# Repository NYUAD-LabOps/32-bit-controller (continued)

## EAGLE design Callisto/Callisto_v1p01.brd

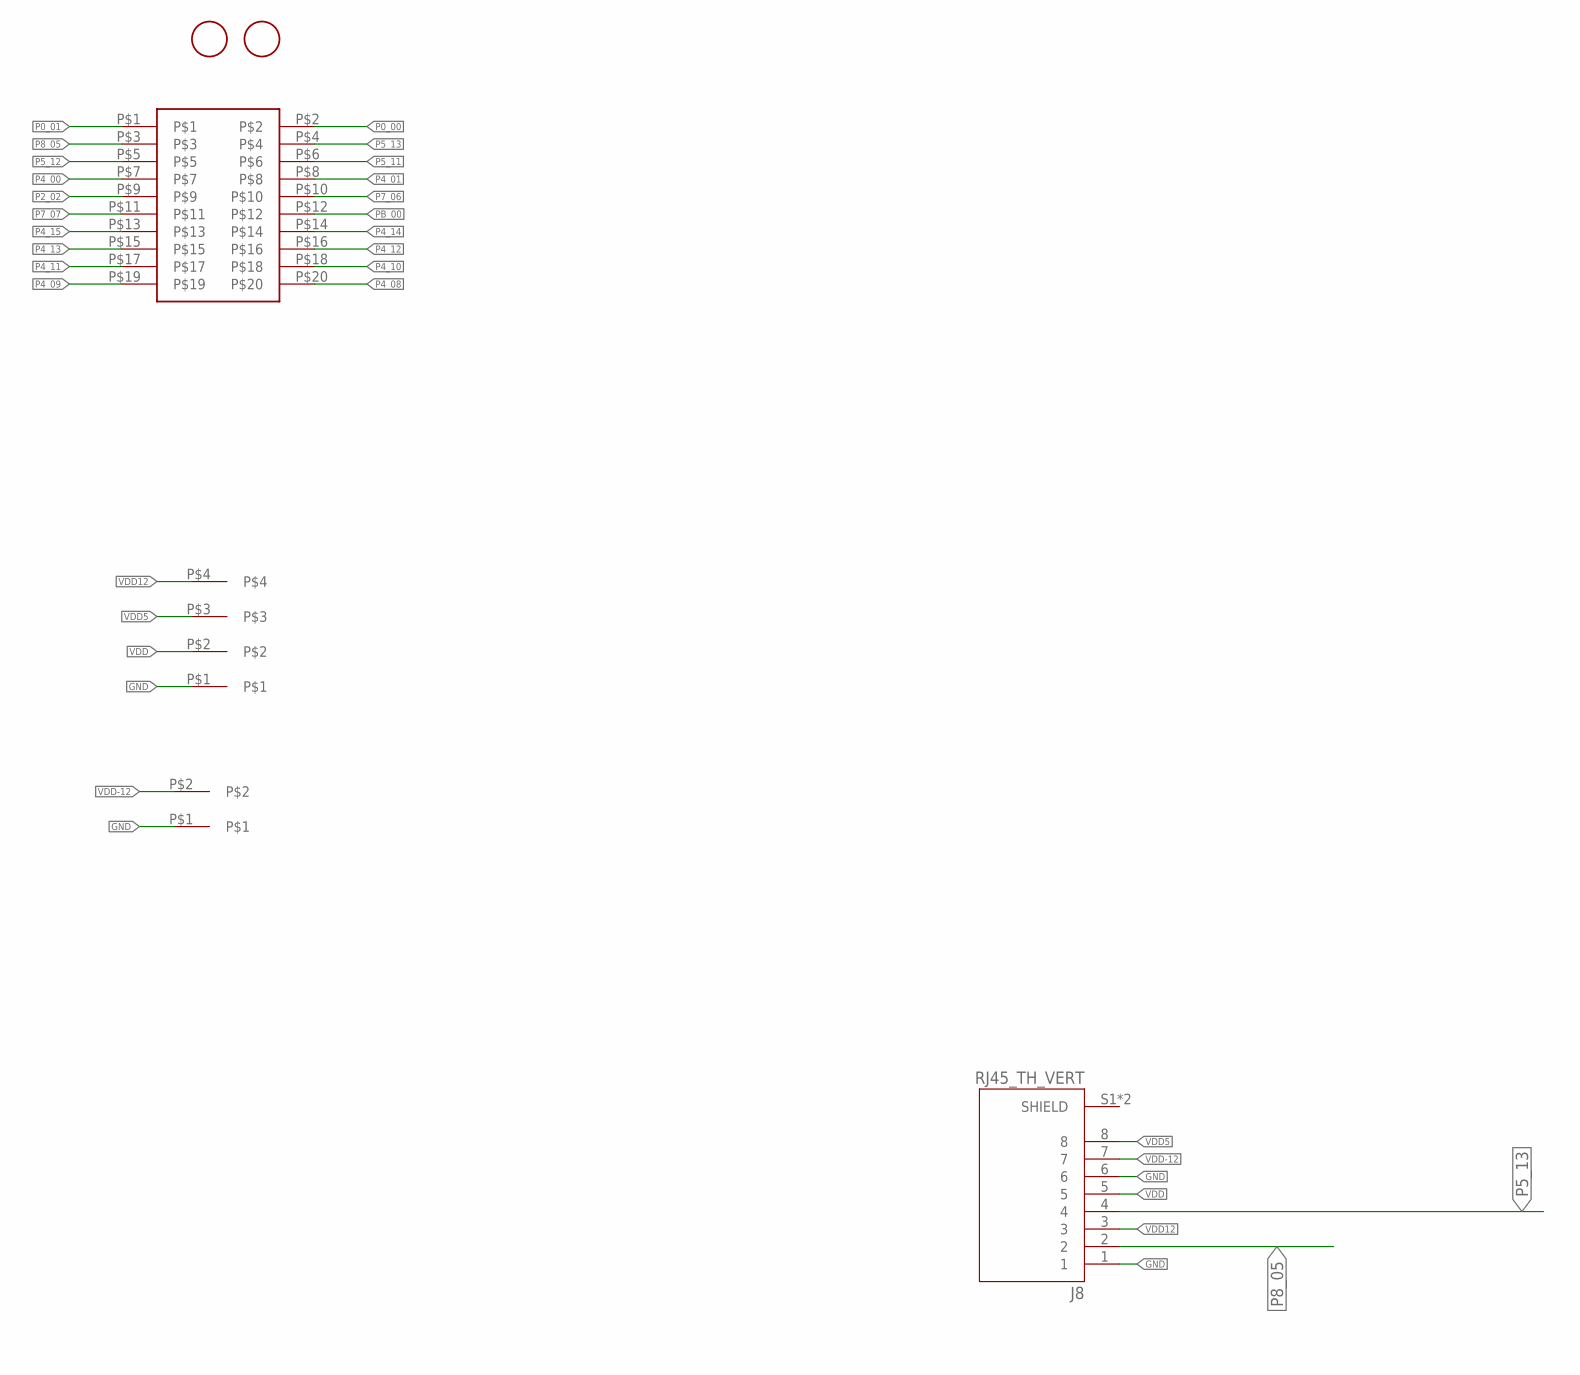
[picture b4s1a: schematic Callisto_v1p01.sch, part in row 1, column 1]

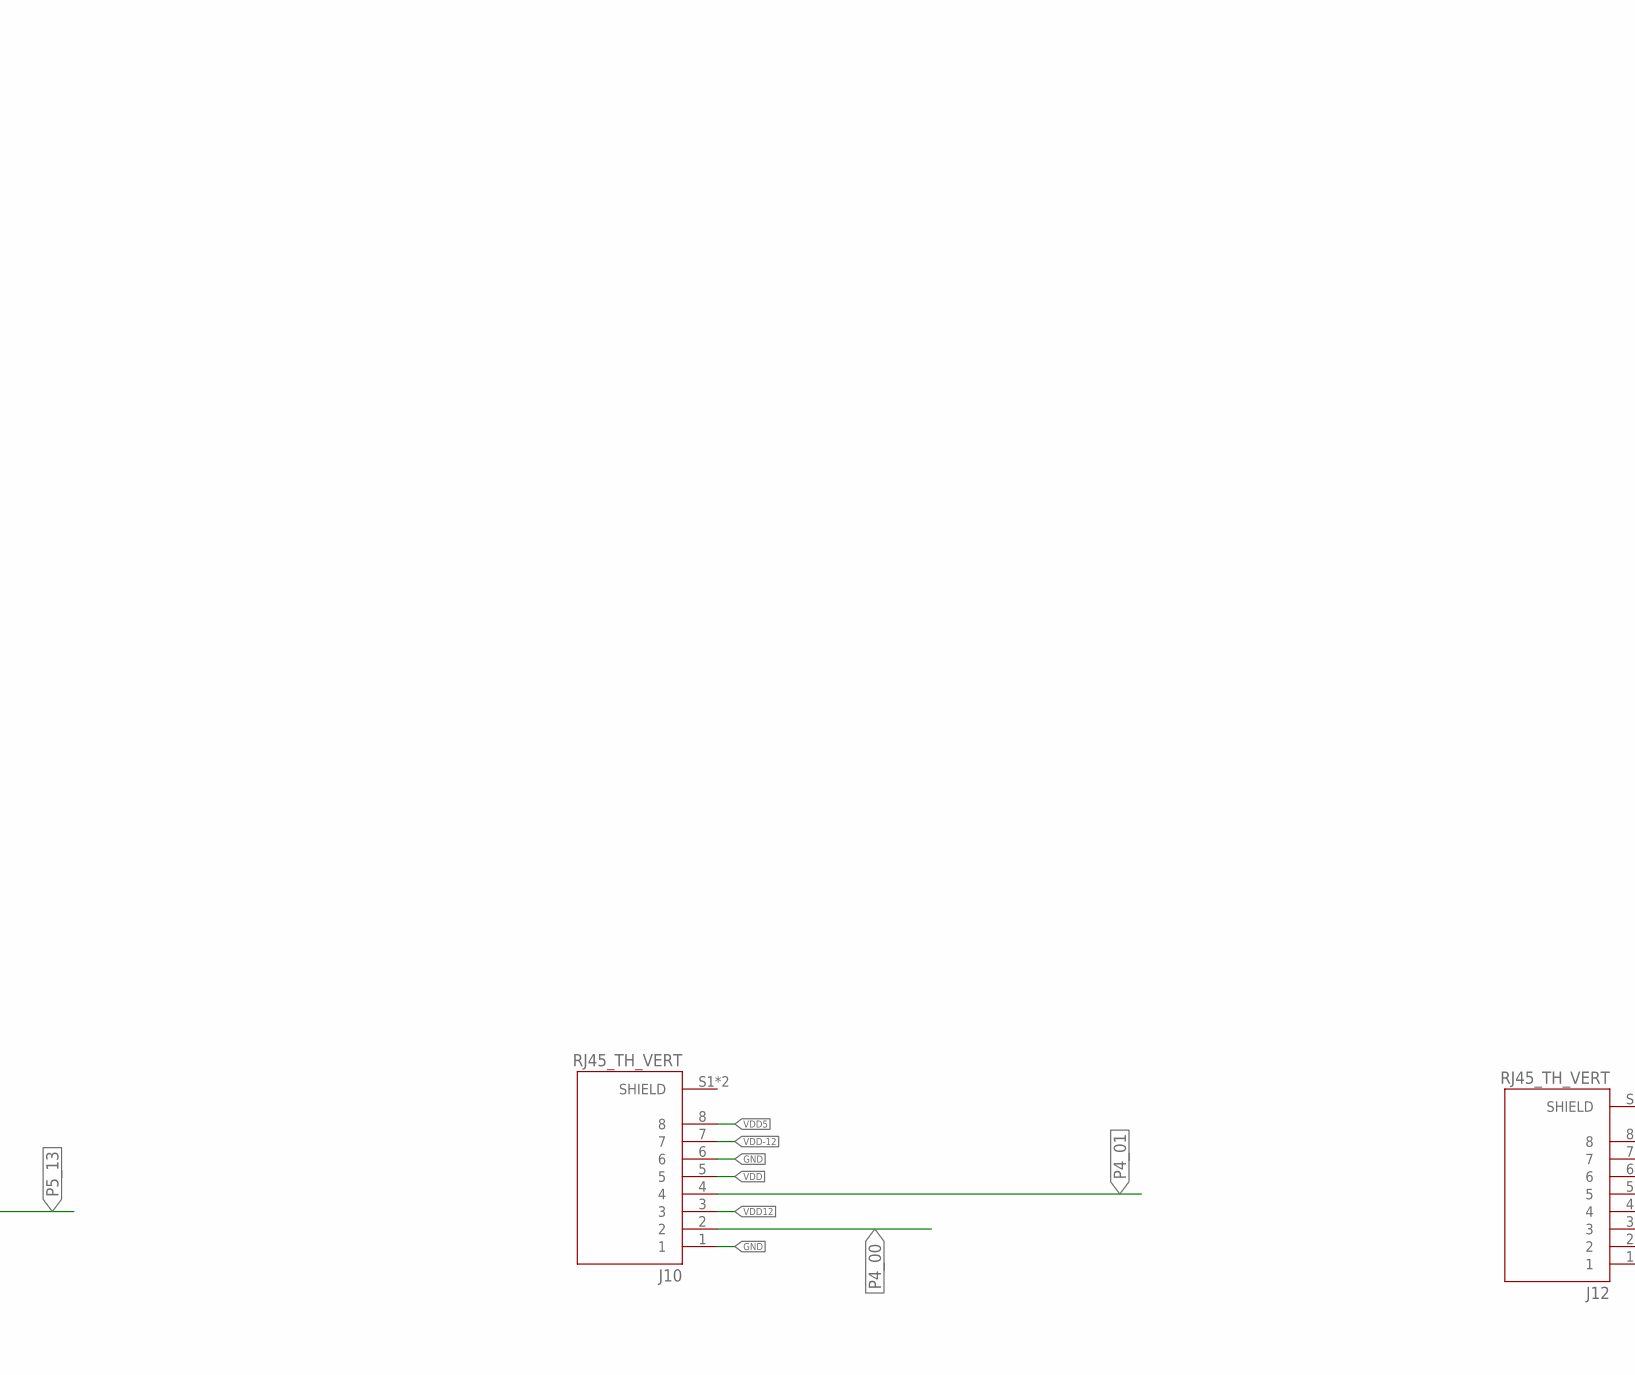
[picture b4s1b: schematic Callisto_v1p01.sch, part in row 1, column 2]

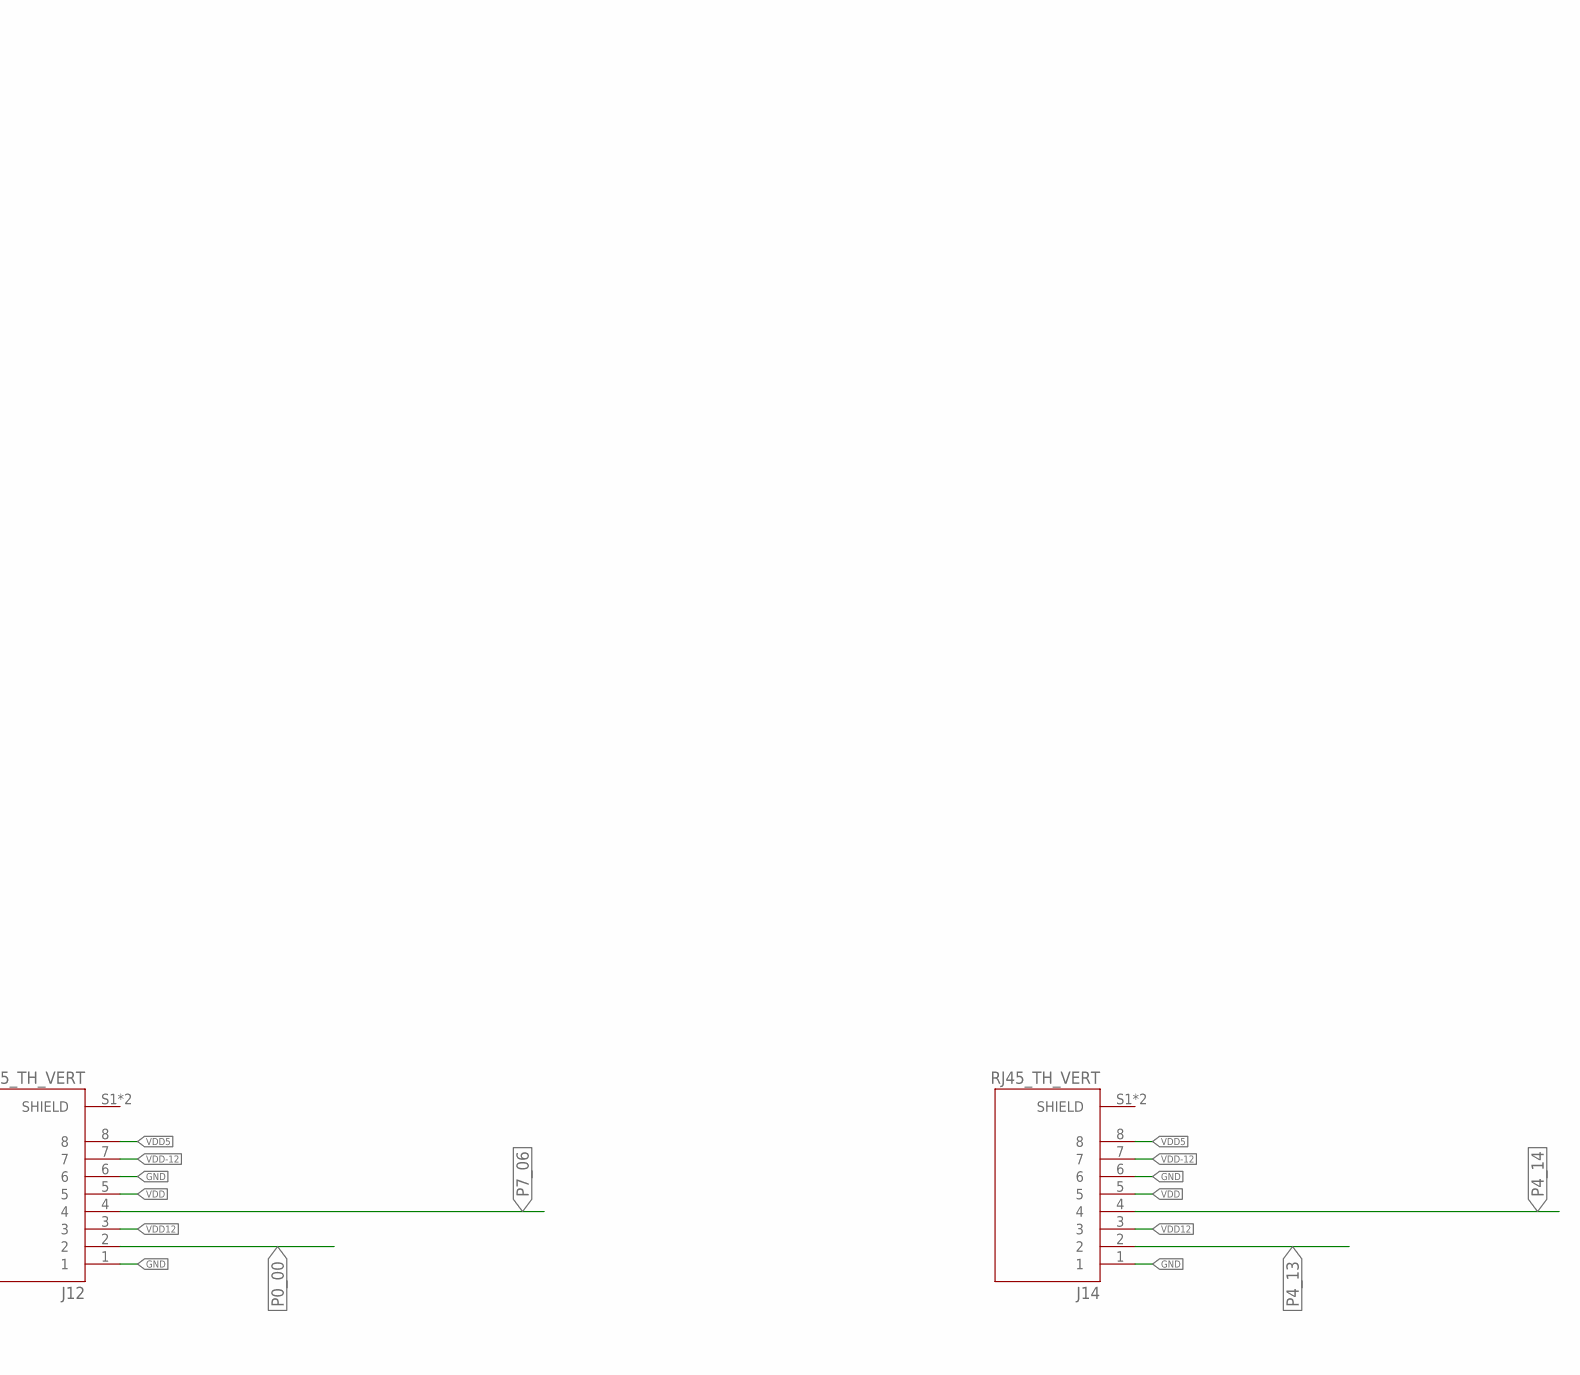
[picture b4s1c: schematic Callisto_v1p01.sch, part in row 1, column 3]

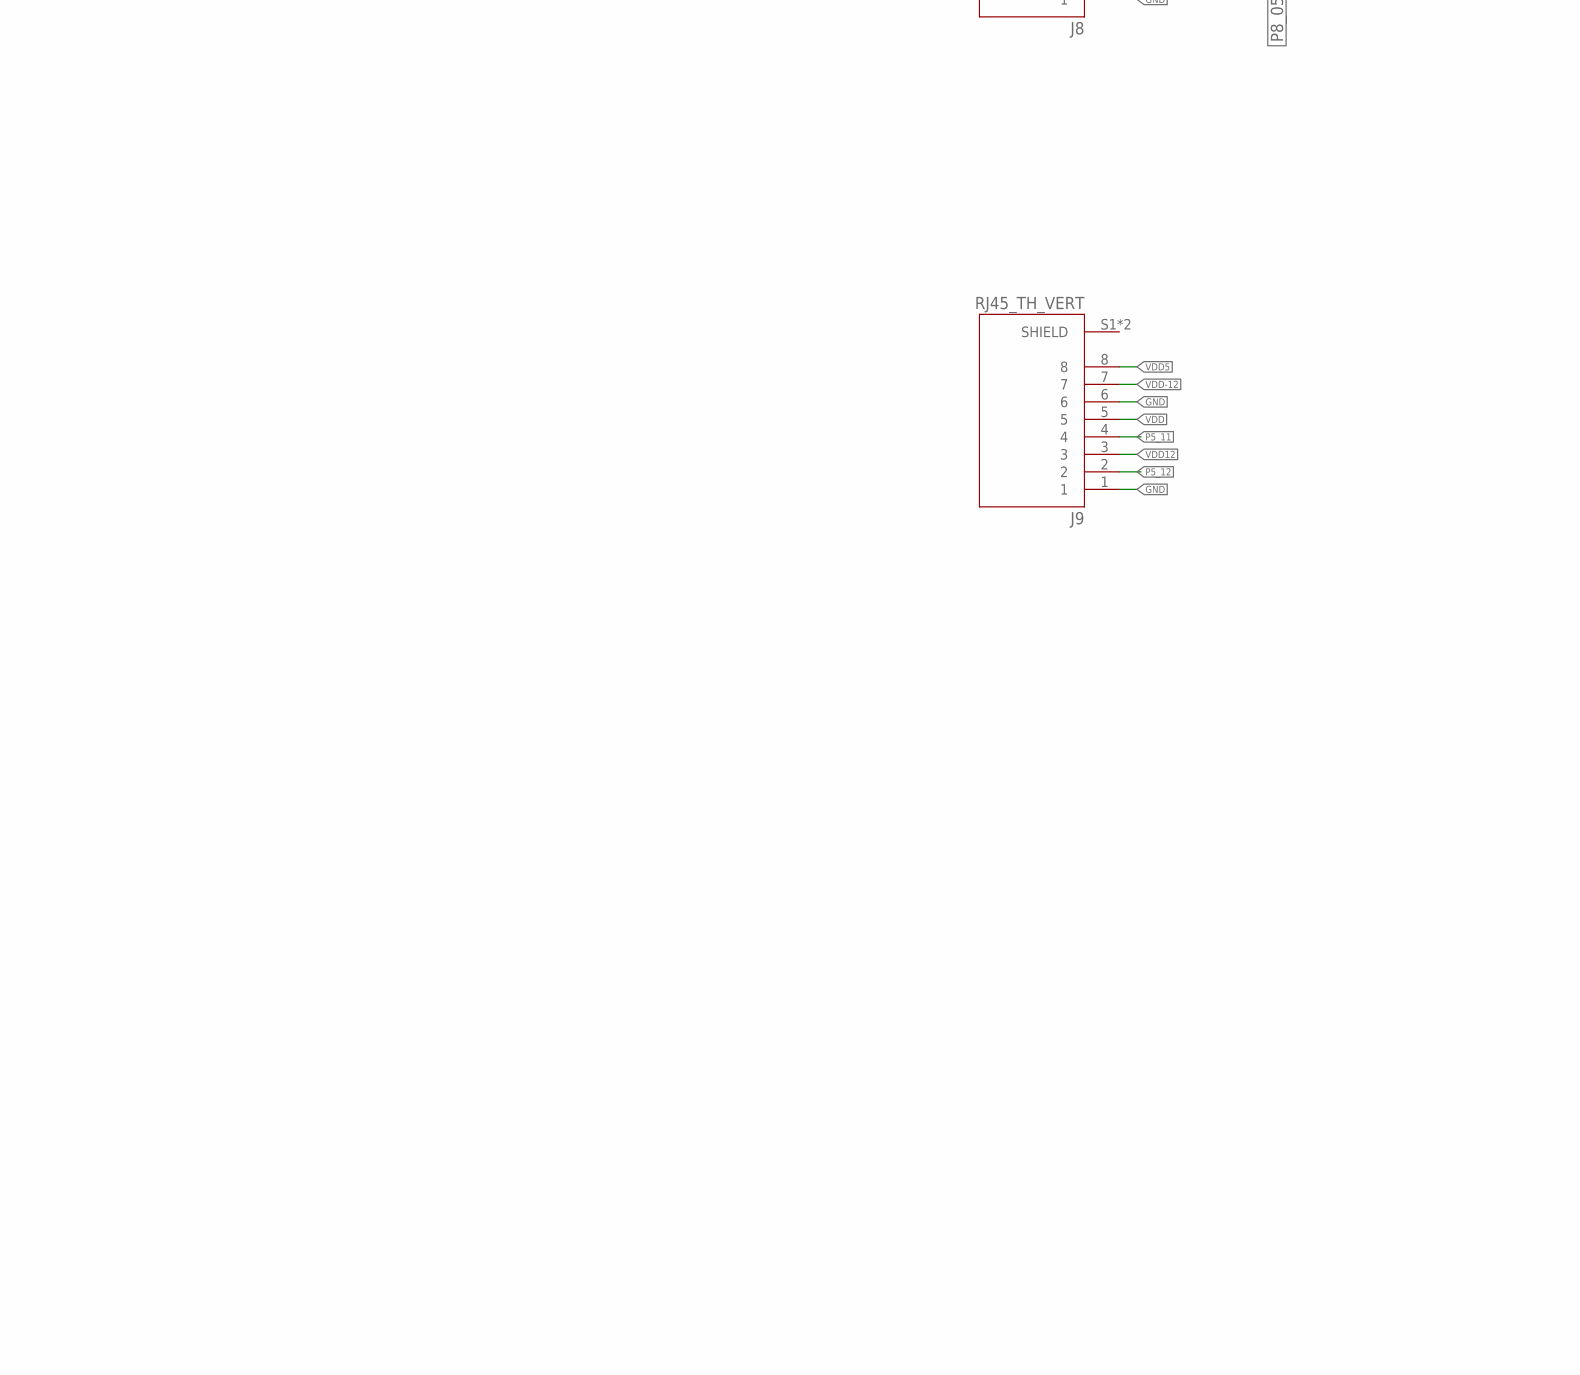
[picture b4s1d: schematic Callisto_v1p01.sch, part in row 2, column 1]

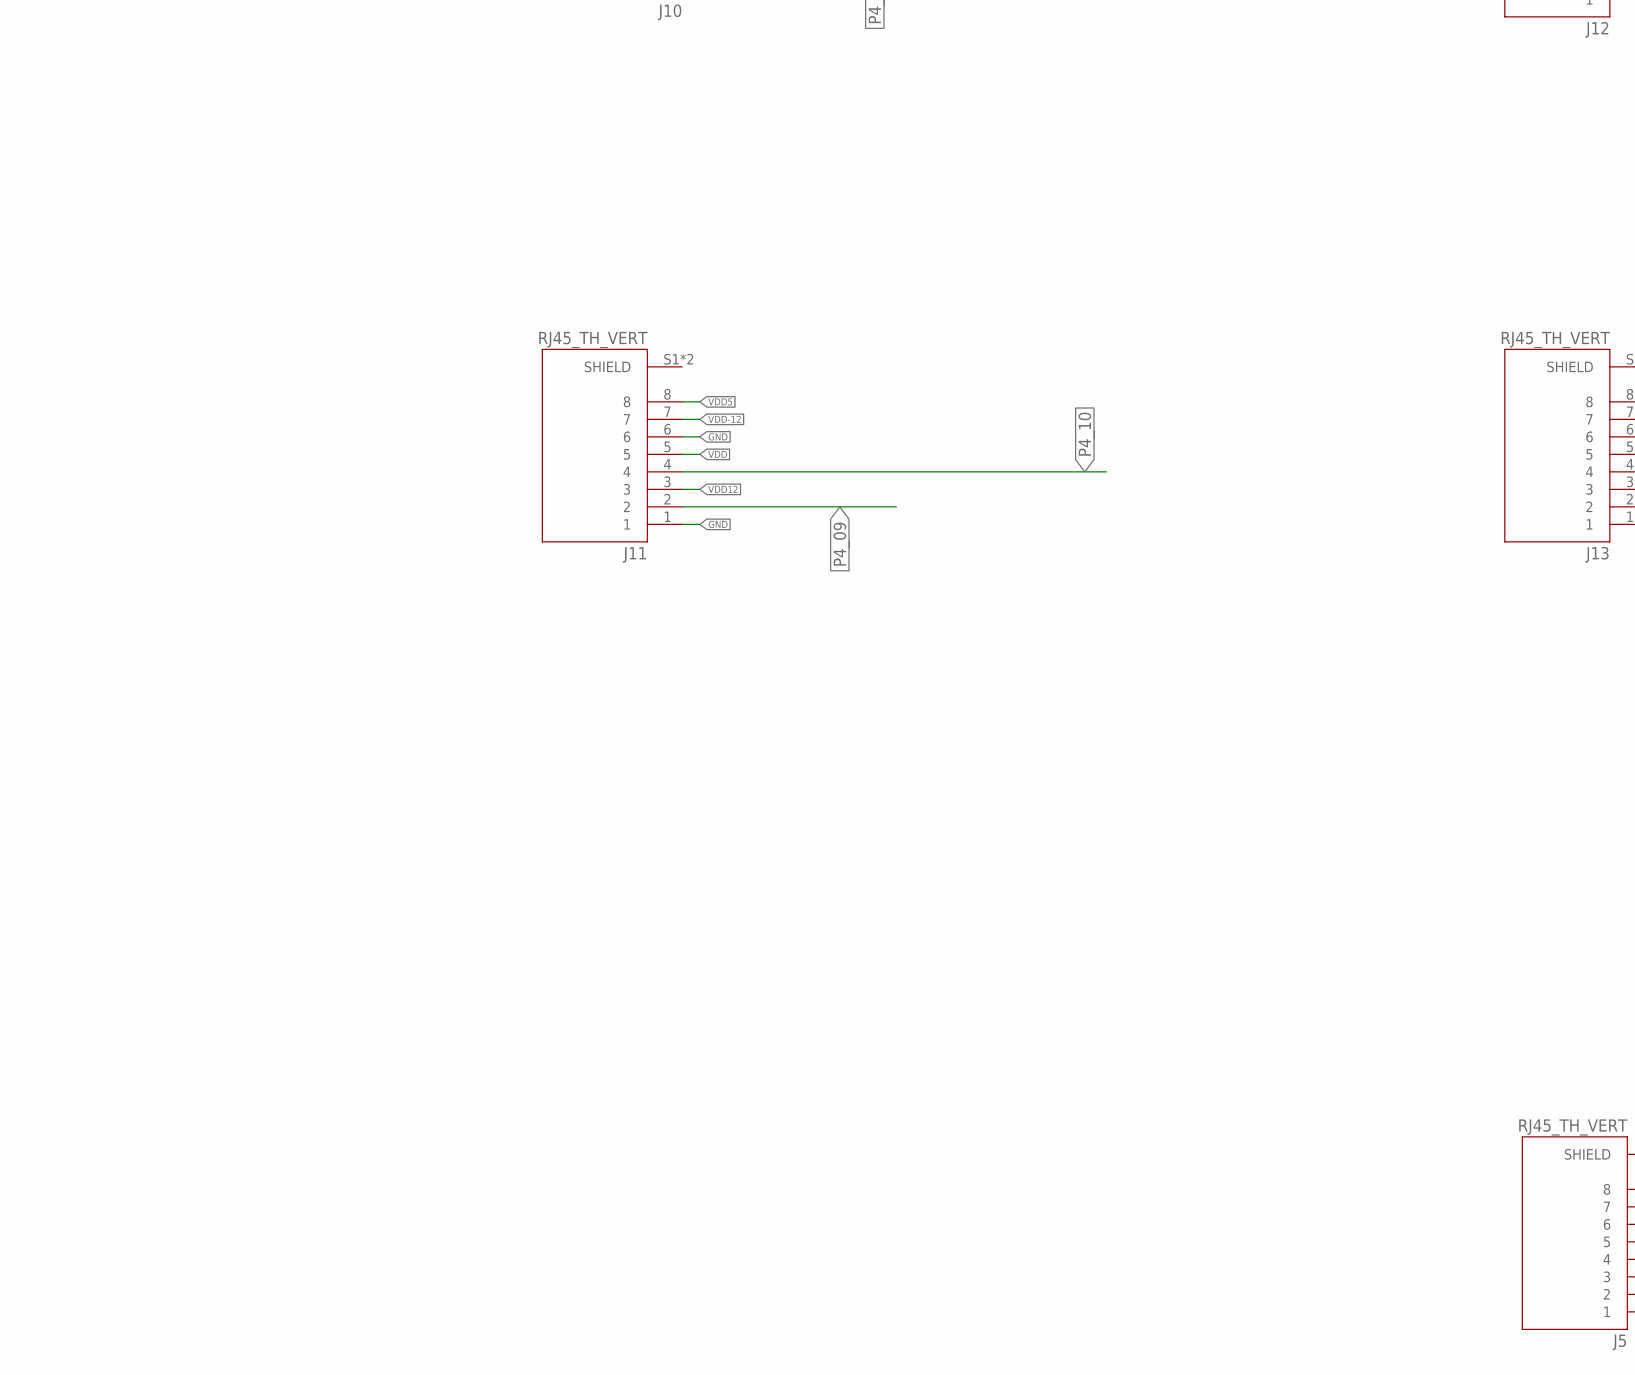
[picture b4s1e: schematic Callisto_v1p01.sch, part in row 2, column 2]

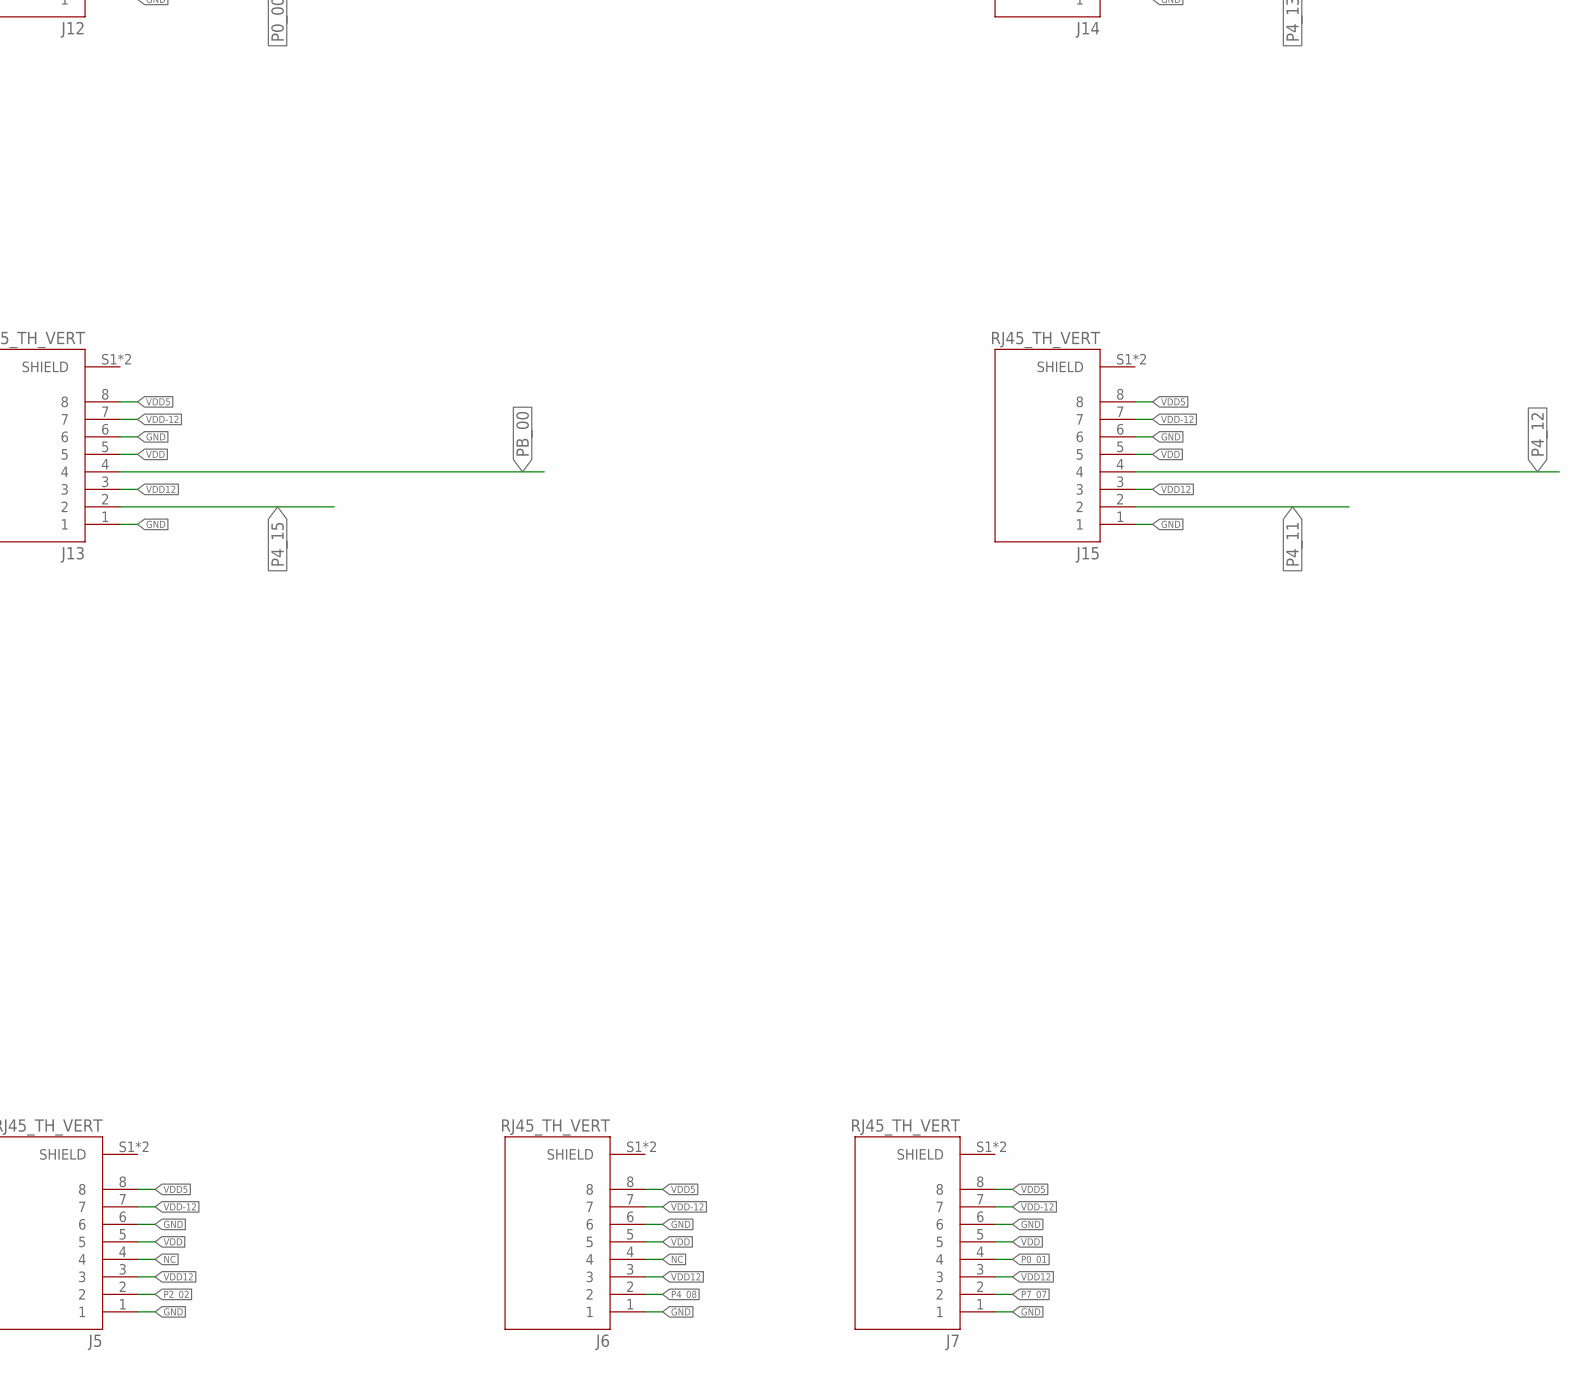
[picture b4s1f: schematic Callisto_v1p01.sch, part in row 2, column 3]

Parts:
J1: 20-pos; 2_X_10_.1_INCH
J2: 2-pos; 2_3.81MM_PITCH
J3: 4-pos; 1X4_3.81MM_PITCH
J5, J6, J7, J8, J9, J10, J11, J12, J13, J14, J15: RJ45_TH_VERT; ASSMANN_A-2014-2S-4-N-R
U$1, U$2: FIDUCIAL_1MM

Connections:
GND: J2.P$1, J3.P$1, J5.1, J5.6, J6.1, J6.6, J7.1, J7.6, J8.1, J8.6, J9.1, J9.6, J10.1, J10.6, J11.1, J11.6, J12.1, J12.6, J13.1, J13.6, J14.1, J14.6, J15.1, J15.6
NC: J5.4, J6.4
P0_00: J1.P$2, J12.2
P0_01: J1.P$1, J7.4
P2_02: J1.P$9, J5.2
P4_00: J1.P$7, J10.2
P4_01: J1.P$8, J10.4
P4_08: J1.P$20, J6.2
P4_09: J1.P$19, J11.2
P4_10: J1.P$18, J11.4
P4_11: J1.P$17, J15.2
P4_12: J1.P$16, J15.4
P4_13: J1.P$15, J14.2
P4_14: J1.P$14, J14.4
P4_15: J1.P$13, J13.2
P5_11: J1.P$6, J9.4
P5_12: J1.P$5, J9.2
P5_13: J1.P$4, J8.4
P7_06: J1.P$10, J12.4
P7_07: J1.P$11, J7.2
P8_05: J1.P$3, J8.2
PB_00: J1.P$12, J13.4
VDD: J3.P$2, J5.5, J6.5, J7.5, J8.5, J9.5, J10.5, J11.5, J12.5, J13.5, J14.5, J15.5
VDD5: J3.P$3, J5.8, J6.8, J7.8, J8.8, J9.8, J10.8, J11.8, J12.8, J13.8, J14.8, J15.8
VDD12: J3.P$4, J5.3, J6.3, J7.3, J8.3, J9.3, J10.3, J11.3, J12.3, J13.3, J14.3, J15.3
VDD-12: J2.P$2, J5.7, J6.7, J7.7, J8.7, J9.7, J10.7, J11.7, J12.7, J13.7, J14.7, J15.7

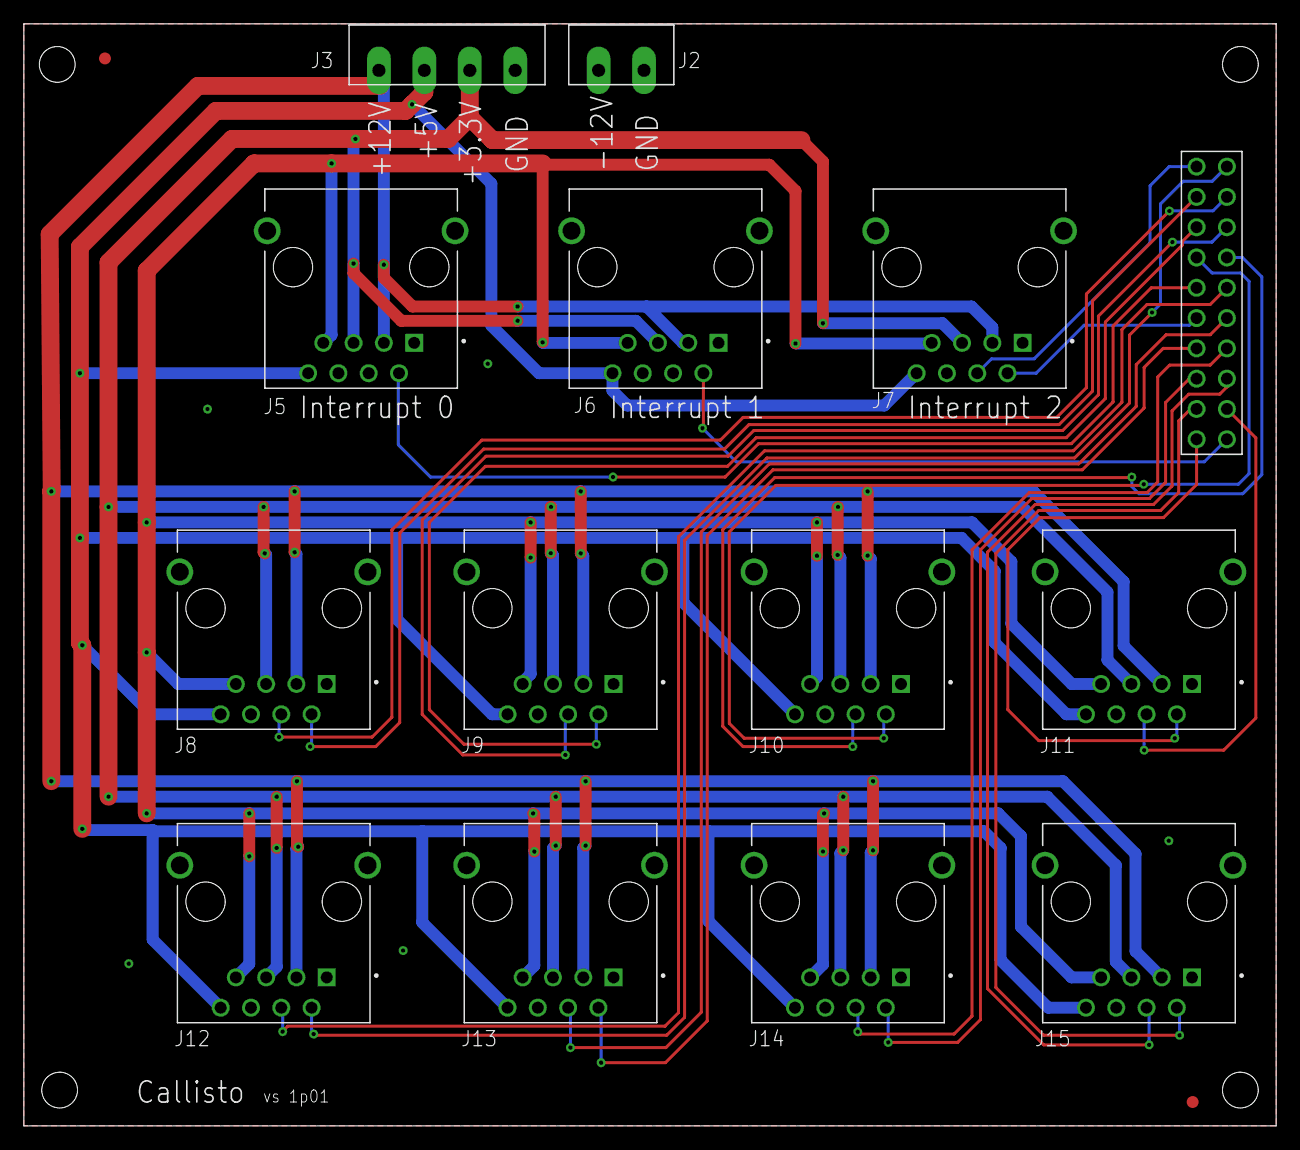
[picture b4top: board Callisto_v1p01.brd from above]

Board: 2 copper layers, 105.0 x 92.4 mm, 16 parts (0 on the bottom side), 26 nets.

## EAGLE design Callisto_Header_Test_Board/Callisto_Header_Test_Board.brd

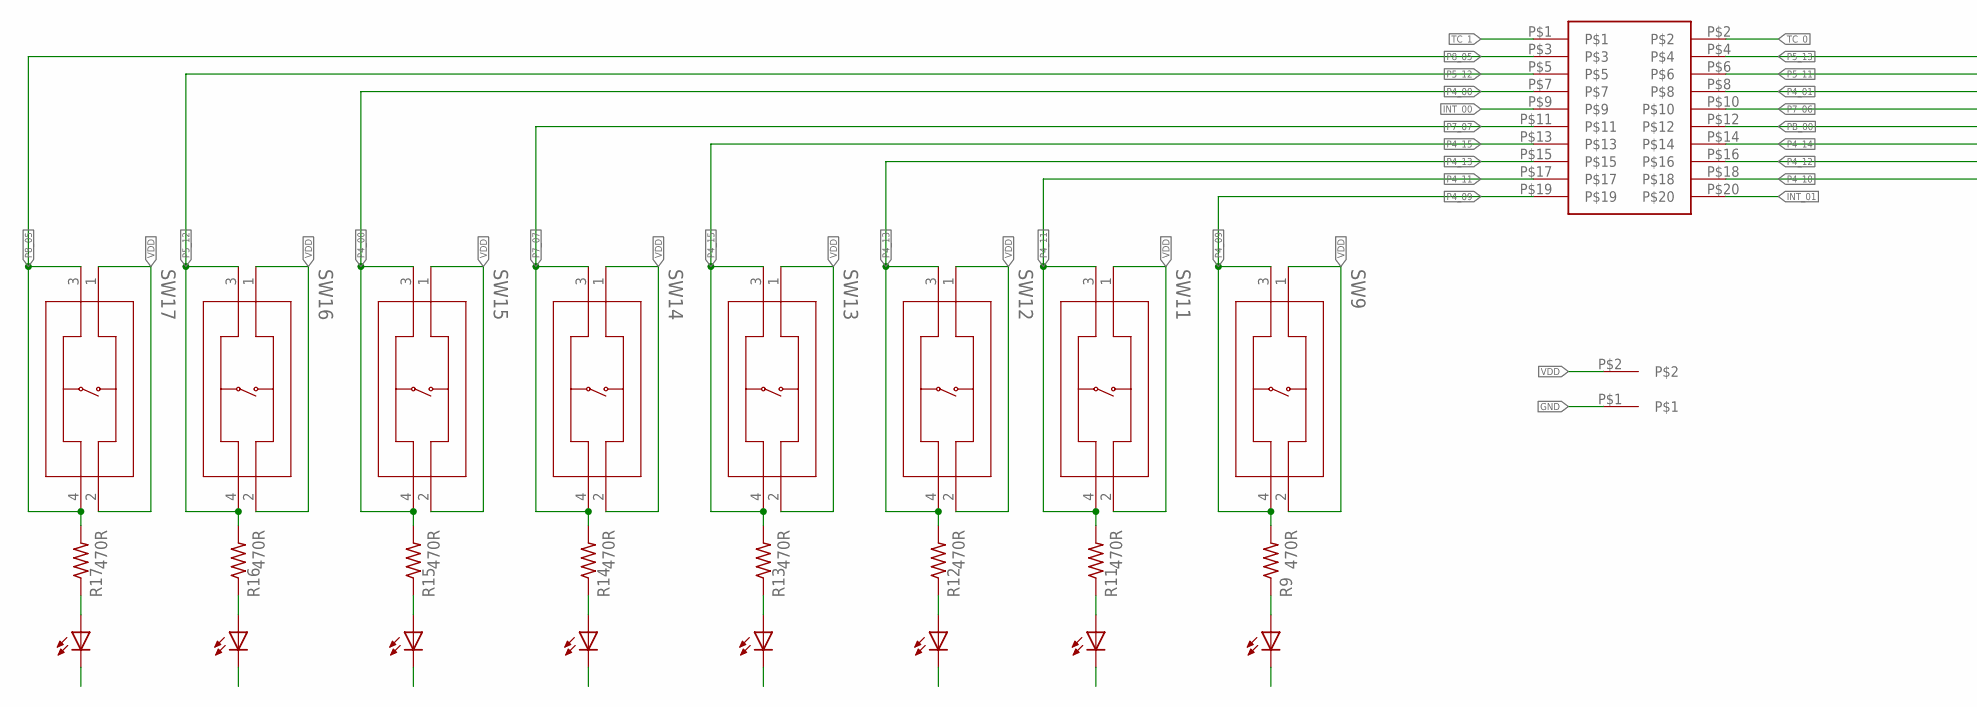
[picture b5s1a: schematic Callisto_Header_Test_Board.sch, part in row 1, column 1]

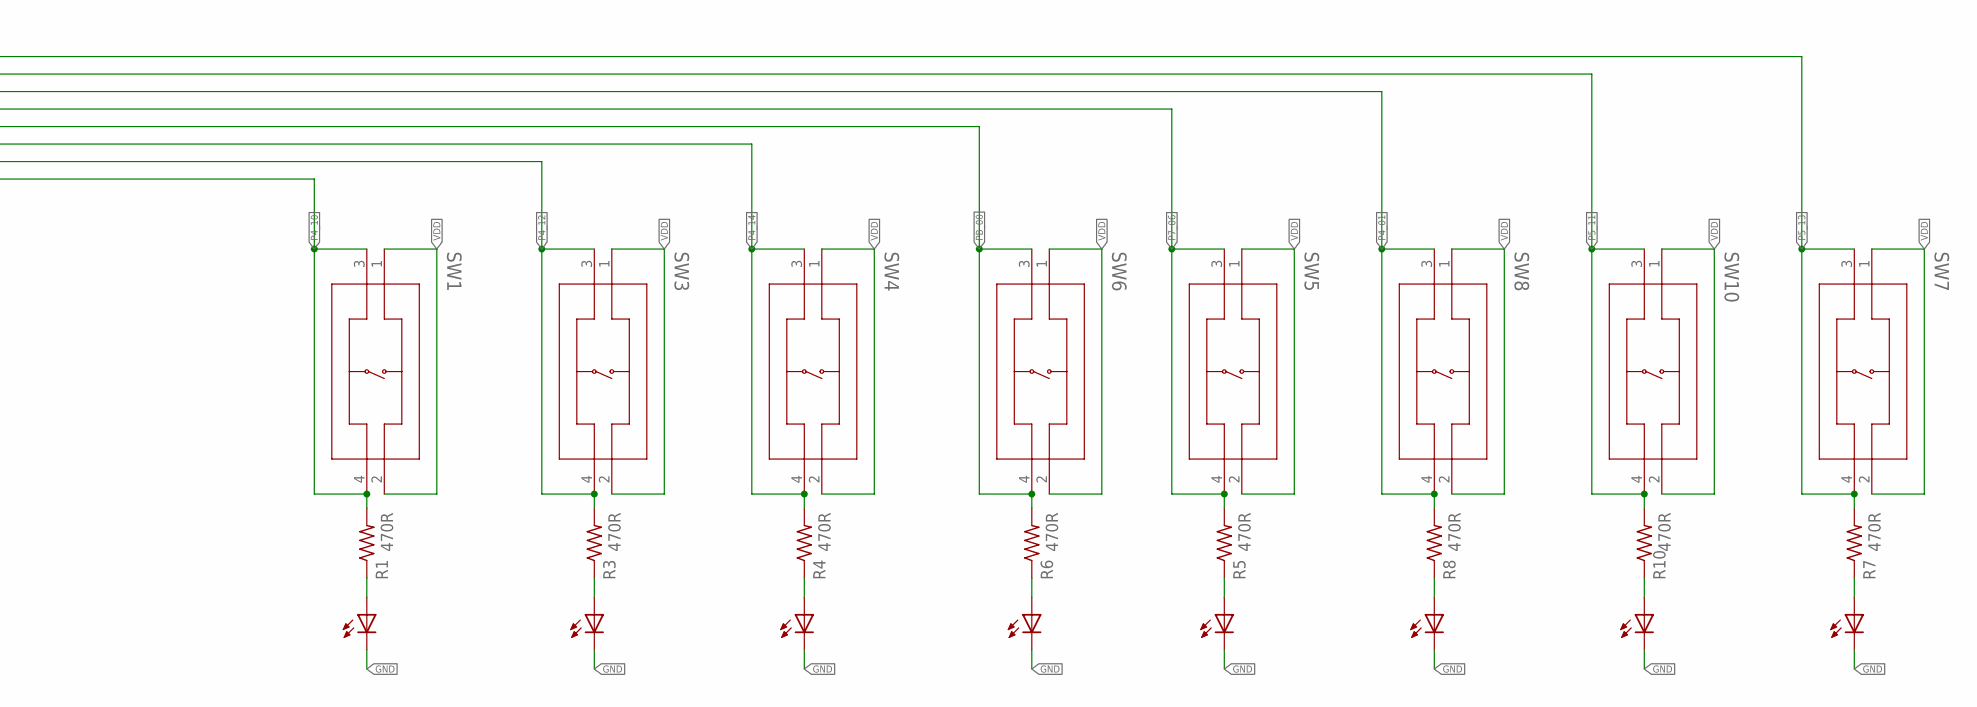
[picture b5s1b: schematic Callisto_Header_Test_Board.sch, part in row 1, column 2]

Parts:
J1: 20-pos; 2_X_10_.1_INCH
J11: 2-pos; 2_3.81MM_PITCH
LED1, LED3, LED4, LED5, LED6, LED7, LED8, LED9, LED10, LED11, LED12, LED13, LED14, LED15, LED16, LED17: Green; 0805
R1, R3, R4, R5, R6, R7, R8, R9, R10, R11, R12, R13, R14, R15, R16, R17: 470R; 0402
SW1, SW3, SW4, SW5, SW6, SW7, SW8, SW9, SW10, SW11, SW12, SW13, SW14, SW15, SW16, SW17: PTS810SJG250SMTRLFS; PTS810

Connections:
GND: J11.P$1, LED1.2 (C), LED3.2 (C), LED4.2 (C), LED5.2 (C), LED6.2 (C), LED7.2 (C), LED8.2 (C), LED9.2 (C), LED10.2 (C), LED11.2 (C), LED12.2 (C), LED13.2 (C), LED14.2 (C), LED15.2 (C), LED16.2 (C), LED17.2 (C)
INT_00: J1.P$9
INT_01: J1.P$20
unnamed: LED1.1 (A), R1.P$1 (1)
unnamed: LED3.1 (A), R3.P$1 (1)
unnamed: LED4.1 (A), R4.P$1 (1)
unnamed: LED5.1 (A), R5.P$1 (1)
unnamed: LED6.1 (A), R6.P$1 (1)
unnamed: LED7.1 (A), R7.P$1 (1)
unnamed: LED8.1 (A), R8.P$1 (1)
unnamed: LED9.1 (A), R9.P$1 (1)
unnamed: LED10.1 (A), R10.P$1 (1)
unnamed: LED11.1 (A), R11.P$1 (1)
unnamed: LED12.1 (A), R12.P$1 (1)
unnamed: LED13.1 (A), R13.P$1 (1)
unnamed: LED14.1 (A), R14.P$1 (1)
unnamed: LED15.1 (A), R15.P$1 (1)
unnamed: LED16.1 (A), R16.P$1 (1)
unnamed: LED17.1 (A), R17.P$1 (1)
P4_00: J1.P$7, R15.P$2 (2), SW15.3, SW15.4
P4_01: J1.P$8, R8.P$2 (2), SW8.3, SW8.4
P4_09: J1.P$19, R9.P$2 (2), SW9.3, SW9.4
P4_10: J1.P$18, R1.P$2 (2), SW1.3, SW1.4
P4_11: J1.P$17, R11.P$2 (2), SW11.3, SW11.4
P4_12: J1.P$16, R3.P$2 (2), SW3.3, SW3.4
P4_13: J1.P$15, R12.P$2 (2), SW12.3, SW12.4
P4_14: J1.P$14, R4.P$2 (2), SW4.3, SW4.4
P4_15: J1.P$13, R13.P$2 (2), SW13.3, SW13.4
P5_11: J1.P$6, R10.P$2 (2), SW10.3, SW10.4
P5_12: J1.P$5, R16.P$2 (2), SW16.3, SW16.4
P5_13: J1.P$4, R7.P$2 (2), SW7.3, SW7.4
P7_06: J1.P$10, R5.P$2 (2), SW5.3, SW5.4
P7_07: J1.P$11, R14.P$2 (2), SW14.3, SW14.4
P8_05: J1.P$3, R17.P$2 (2), SW17.3, SW17.4
PB_00: J1.P$12, R6.P$2 (2), SW6.3, SW6.4
TC_0: J1.P$2
TC_1: J1.P$1
VDD: J11.P$2, SW1.1, SW1.2, SW3.1, SW3.2, SW4.1, SW4.2, SW5.1, SW5.2, SW6.1, SW6.2, SW7.1, SW7.2, SW8.1, SW8.2, SW9.1, SW9.2, SW10.1, SW10.2, SW11.1, SW11.2, SW12.1, SW12.2, SW13.1, SW13.2, SW14.1, SW14.2, SW15.1, SW15.2, SW16.1, SW16.2, SW17.1, SW17.2

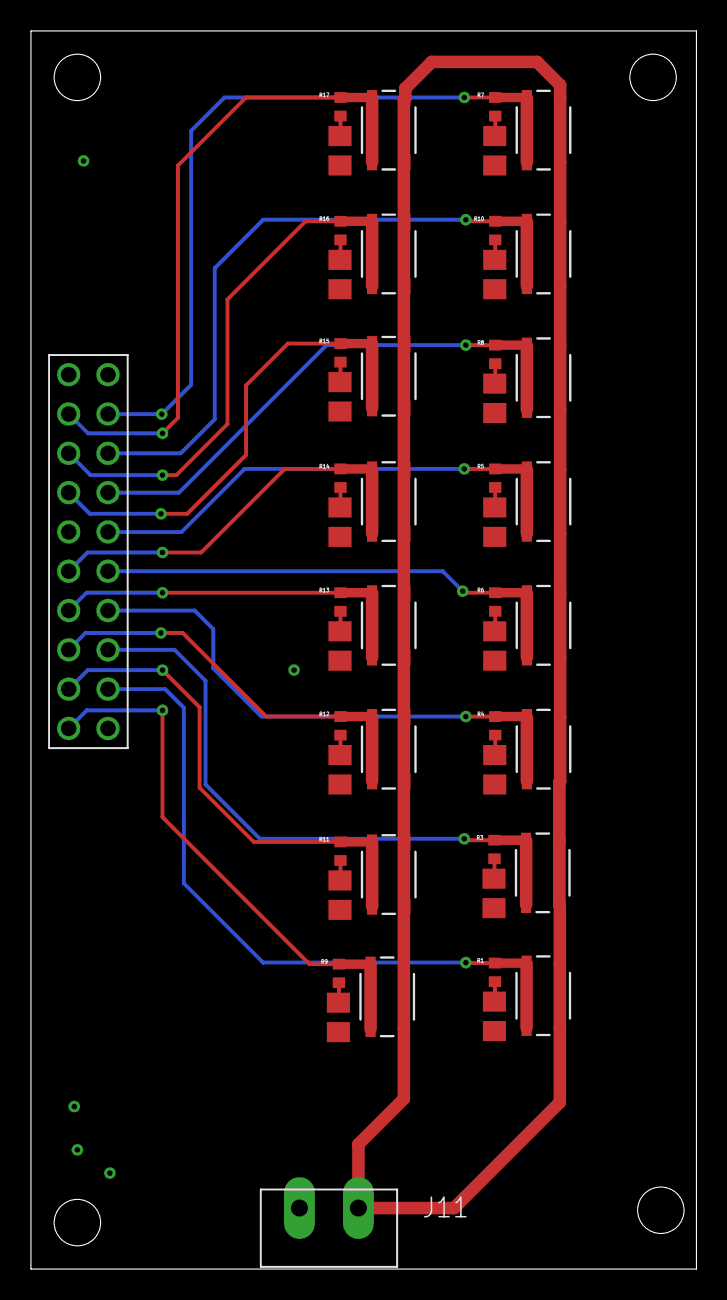
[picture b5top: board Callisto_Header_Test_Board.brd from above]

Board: 2 copper layers, 43.0 x 80.0 mm, 50 parts (0 on the bottom side), 34 nets.

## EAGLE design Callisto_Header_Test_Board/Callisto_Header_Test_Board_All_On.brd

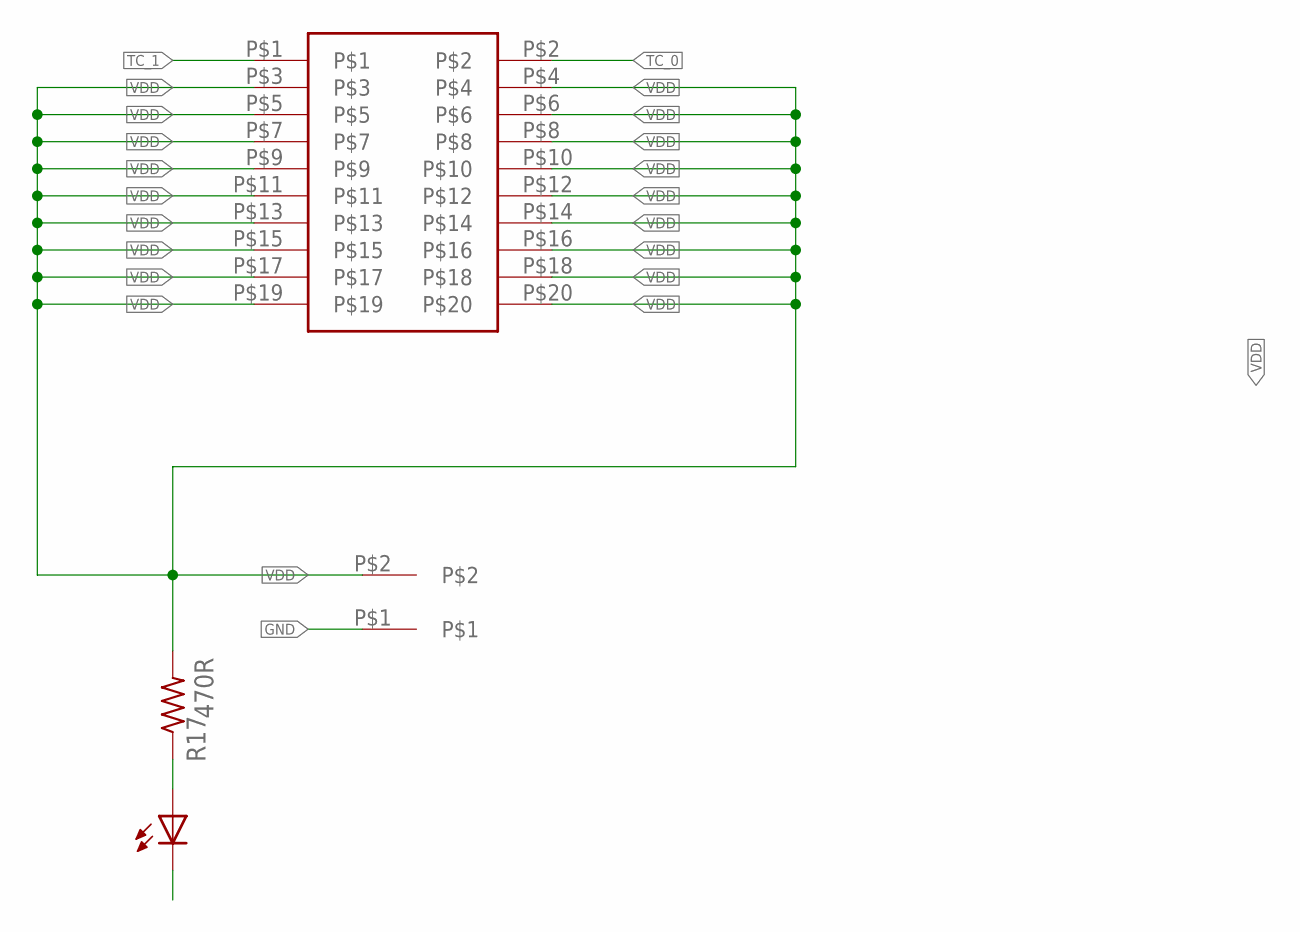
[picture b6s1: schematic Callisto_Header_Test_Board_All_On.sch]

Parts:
J1: 20-pos; 2_X_10_.1_INCH
J11: 2-pos; 2_3.81MM_PITCH
LED17: Green; 0805
R17: 470R; 0402

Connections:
GND: J11.P$1, LED17.2 (C)
unnamed: LED17.1 (A), R17.P$1 (1)
TC_0: J1.P$2
TC_1: J1.P$1
VDD: J1.P$3, J1.P$4, J1.P$5, J1.P$6, J1.P$7, J1.P$8, J1.P$9, J1.P$10, J1.P$11, J1.P$12, J1.P$13, J1.P$14, J1.P$15, J1.P$16, J1.P$17, J1.P$18, J1.P$19, J1.P$20, J11.P$2, R17.P$2 (2)
